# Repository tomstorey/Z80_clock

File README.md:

# Z80 based, triple time zone clock

This repository contains design files and source code for a clock project which uses a Z80 processor, and can display upto three different time zones at once.

All code is written in Z80 assembly, and can be assembled with the zasm assembler available at:

https://k1.spdns.de/Develop/Projects/zasm/Distributions/

Other assemblers may work, perhaps with minor modification to the code.

The display is made up of three rows of eight 16-segment displays, and is driven by a shift register of 136 bits (128 for display segments plus 8 for the dot points of the displays) so that an entire row is driven all at once.

Within the clock is a [Texas Instruments BQ4845 Real Time Clock](http://www.ti.com/product/BQ4845). A backup battery maintains the time while the power is off. The RTC time and date is configured to represent UTC, and each time zone is then calculated as an offset from UTC, either positive or negative.

Three ROMs provide all of the non-volatile storage needs:

 1. App ROM contains the application code
 2. TZ ROM contains time zone information
 3. Char ROM contains data for displaying characters

The following table describes the address ranges covered by each of the memories:

|              | Start  | End    | Size |
| ------------ | ------:| ------:| ----:|
| **App ROM**  | 0x0000 | 0x5FFF |  24K |
| **RAM**      | 0x6000 | 0x9FFF |  16K |
| **TZ ROM**   | 0xC000 | 0xDFFF |   8K |
| **Char ROM** | 0xE000 | 0xFFFF |   8K |

DIP switches allow each row of the display to be configured to any time or date according to entries stored within the TZ ROM.

## Source code structure/explanation
Assembly source files end with the `.s` extension. `.inc` files provide defines/equates and macros.

`clock.s` is the top source file, which includes a variety of `.inc` and other `.s` files to build up the entire application.

Other files in no particular order:

`configr_app.s` implements an "application" of sorts which allows the user to configure the time and date of the RTC.

`clock_app.s` also implements an "application" of sorts, the clock itself.

`c_lib.s` is an implementation of a couple of C-esque functions to copy blocks of memory and null terminated strings.

`ctc_isr.s` is where all of the Interrupt Service Routines for the CTC timer/counter channels live.

`platform.inc` provides information about the memory locations and sizes - this was particularly important during development as I was using a custom serial loader (`serial_mon.s`) to transfer and execute code from RAM, and needed to define different memory locations and sizes based on whether the code was assembled for serial loading or not.

`clock.inc` provides a lot of detail about the clock hardware, such as the addresses of various I/O peripherals. Included are also a variety of macros that provide basic mutex and sempahore functionality, among others.

Other `.inc` files define setting for control registers of various peripherals.

### Software architecture notes
The software implements some rudimentary "task" infrastructure intended to make it more modular and easily maintainable.

To achieve this, some macros are provided for scheduling and descheduling "tasks" and "applications". Although they are essentially the same thing, I have two basic rules to differentiate them:

 - Tasks are scheduled and descheduled to run only when required
 - Applications should be scheduled and never descheduled

For example, the configr and clock tasks are considered two applications because they are scheduled when the clock starts up, and never technically descheduled, however, only one of them will "run" at any one time, which brings me to the next topic...

Basic locking and signalling infrastructure is also provided through some semaphore and mutex macros.

Semaphores can be used to signal one piece of code from another piece of code. A specific example of the use of semaphores in this clock is between the clock application and the per-minute ISR from the RTC. The clock app signals to the ISR that it wants to know when the per-minute interrupt has occurred, and the ISR reciprocates by signalling to the application that it has occurred. This is achieved through two semaphores: 1. for the application to signal it wants to know when an interrupt has occurred, 2. for the ISR to signal the interrupt has occurred. Other uses of semaphores include signalling to various tasks when they should run.

Mutexes are used to lock resouces so that only one piece of code may use them at any one time. A particular use of mutexes in this clock is to determine which application "owns the foreground", or in other words, who can write to display buffers and read button states. The first application to acquire the foreground mutex can then hold onto it for as long as it wants (usually until the user presses the Esc button to switch between the clock and the configr apps).

### Utilities

There are a couple of small Python based utilities included as well, which were used during development, and in conjunction with `serial_mon.s`:

`loader.py` is used to load a `.rom` (i.e. binary) file into RAM and optionally execute it. This tool was used heavily and has had the most development. Each time I would build a new version of the clock software I would hit the reset button and use this tool to load the code into RAM and execute it.

`execer.py` is essentially the execute portion of the above, and simply tells the serial monitor to jump to a certain address. Could be used after a reset to simply re-execute the code without having to reload it.

`sender.py` is used to send bytes, and was used mostly during development of the serial monitor itself.

`reader.py` was intended to provide an ability to read back a portion of memory, but is in an unknown state at this time and the matching functionality is not implemented in the current serial loader.

## Hardware designs/schematics
Hardware designs are functional and complete. There are no PCB designs as the prototype hardware was built as rats nest on proto boards.

At time of writing, the following TODO list remains:

 - Determine best way to drive the speaker - there is a free CTC channel which could be used for this?

Otherwise, here are some lightweight descriptions of the schematic files:

`CPU board *.sch` contains the processor and all memories (RAM/ROMs), reset circuitry, oscillator, and power input.

`timer rtc io.sch` is a module which contains the RTC, a Z80 CTC peripheral, and user interface inputs such as buttons and DIP switches. It also has the speaker. The RTC also includes a watchdog reset function.

`display driver rev X.sch` contains all of the shift registers to drive all display segments on one row. Rev A implemented a discrete parallel-load to serial-output peripheral with 74HC595 shift registers for the drivers. Rev B changed the shift registers to TLC5916's (proper LED drivers) and also uses an ATF1502AS CPLD to implement the shift register logic. Both boards are functionally equivalent in that the CPU can simply OUT a byte and the shifter will automatically shift the byte out. Char ROM data may need to be inverted depending on which revision is in use - something I should probably make consistent, but notes are included in the char_rom.s file to help you figure that out in the mean time.

`uart board.sch` contains a Z80 SIO peripheral which was used for serial loading of code for execution from RAM. In a future revision I'll likely repurpose this to interface with a GPS module to perform time synchronisation to compensate for drift in the RTC.

There is currently no real schematic for the display board itself, this is a work in progress. I'll get around to it some day. :-)

## z80clock on MAME

A [MAME driver](https://github.com/mamedev/mame/blob/master/src/mame/drivers/z80clock.cpp)
to emulate for this project was added by
[Phill (@smf)](https://github.com/smf-) for his
[Using MAME as a development tool](https://www.meetup.com/london-retro-computing/events/282682483/)
presentation to the
[London Retro Computing Meetup](https://www.meetup.com/london-retro-computing/)

If you don't already have MAME get it from
[MAMEdev.org](https://www.mamedev.org/). The z80clock driver has been present
since MAME 0.239.

To run the driver:

```
mame z80clock -cart1 clock.rom -cart2 tz_rom.rom -cart3 char_rom.rom
```

Assuming the roms (in the `source` directory) are in the current directory
and `mame` is on the path.

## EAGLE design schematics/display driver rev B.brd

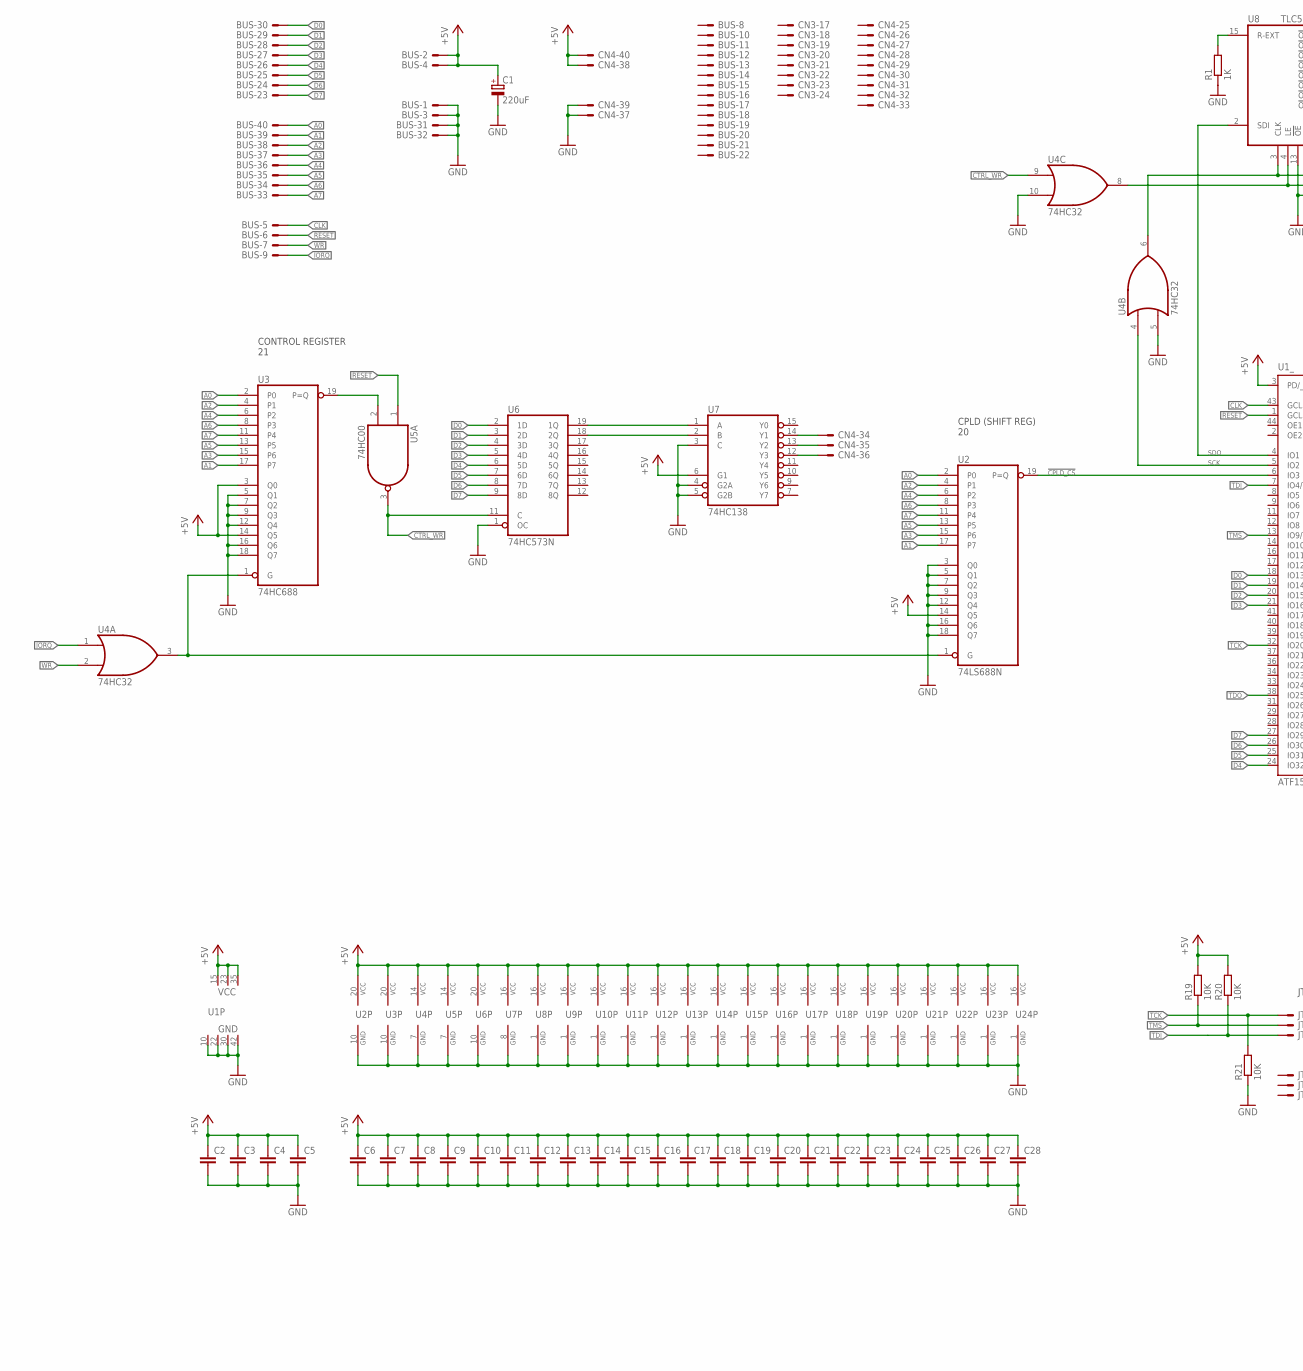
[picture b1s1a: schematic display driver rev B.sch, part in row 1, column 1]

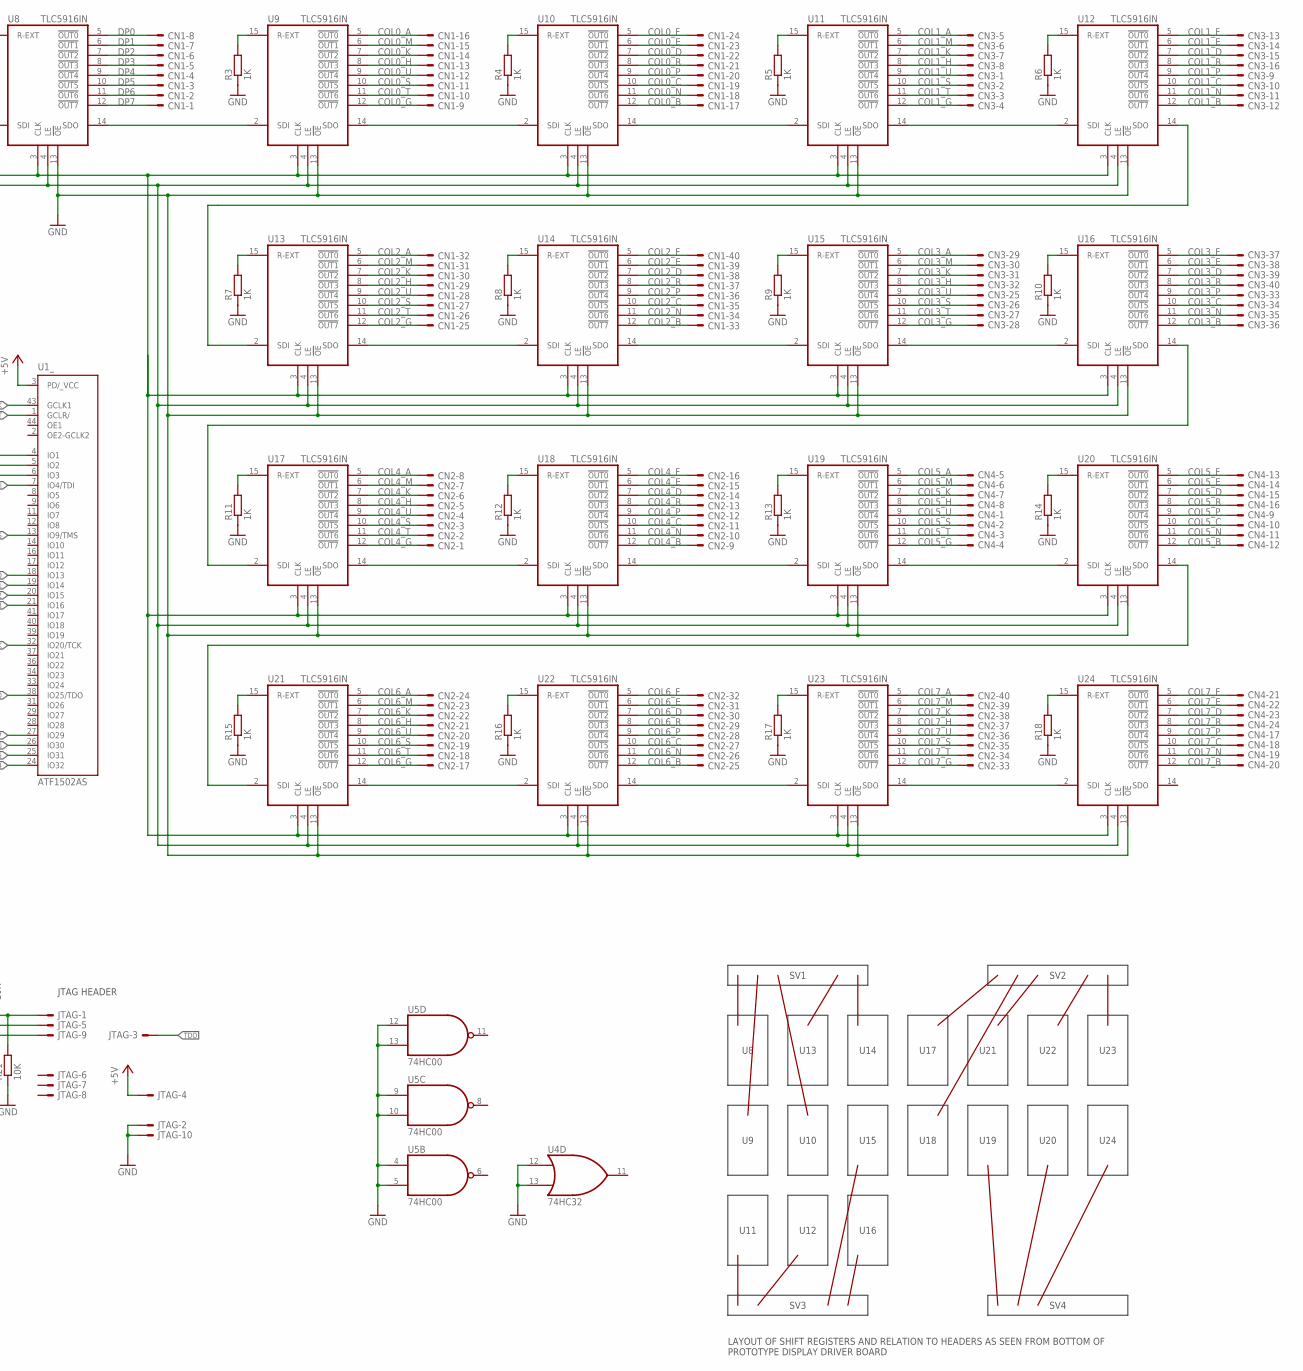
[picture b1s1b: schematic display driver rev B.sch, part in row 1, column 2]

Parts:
BUS: HDR40
C1: 220uF; E3,5-8
C2, C3, C4, C5, C6, C7, C8, C9, C10, C11, C12, C13, C14, C15, C16, C17, C18, C19, C20, C21, C22, C23, C24, C25, C26, C27, C28: C-EU050-025X075; C050-025X075
CN1, CN2, CN3, CN4: HDR40
JTAG: ML10E; ML10
R1, R3, R4, R5, R6, R7, R8, R9, R10, R11, R12, R13, R14, R15, R16, R17, R18: 1K; 0207/10
R19, R20, R21: 10K; 0207/10
U1: ATF1502AS; PLCC-S44
U2: 74LS688N; DIL20
U3: 74HC688; DIL20
U4: 74HC32; DIL14
U5: 74HC00; DIL14
U6: 74HC573N; DIL20
U7: 74HC138; DIL16
U8, U9, U10, U11, U12, U13, U14, U15, U16, U17, U18, U19, U20, U21, U22, U23, U24: TLC5916IN; DIL16

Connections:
!CPLD_CS!: U1.6 (IO3), U2.19 (P=Q)
!CTRL_WR!: U4.9 (I0), U5.3 (O), U6.11 (C)
!IORQ!: BUS.9, U4.1 (I0)
!RESET!: BUS.6, U1.1 (GCLR/), U5.1 (I0)
!WR!: BUS.7, U4.2 (I1)
+5V: BUS.2, BUS.4, C1.+, C2.1, C3.1, C4.1, C5.1, C6.1, C7.1, C8.1, C9.1, C10.1, C11.1, C12.1, C13.1, C14.1, C15.1, C16.1, C17.1, C18.1, C19.1, C20.1, C21.1, C22.1, C23.1, C24.1, C25.1, C26.1, C27.1, C28.1, CN4.38, CN4.40, JTAG.4, R19.2, R20.2, U1.3 (PD/_VCC), U1.15 (VCC), U1.23 (VCC), U1.35 (VCC), U2.14 (Q5), U2.20 (VCC), U3.3 (Q0), U3.14 (Q5), U3.20 (VCC), U4.14 (VCC), U5.14 (VCC), U6.20 (VCC), U7.6 (G1), U7.16 (VCC), U8.16 (VCC), U9.16 (VCC), U10.16 (VCC), U11.16 (VCC), U12.16 (VCC), U13.16 (VCC), U14.16 (VCC), U15.16 (VCC), U16.16 (VCC), U17.16 (VCC), U18.16 (VCC), U19.16 (VCC), U20.16 (VCC), U21.16 (VCC), U22.16 (VCC), U23.16 (VCC), U24.16 (VCC)
A0: BUS.40, U2.2 (P0), U3.2 (P0)
A1: BUS.39, U2.17 (P7), U3.17 (P7)
A2: BUS.38, U2.4 (P1), U3.4 (P1)
A3: BUS.37, U2.15 (P6), U3.15 (P6)
A4: BUS.36, U2.6 (P2), U3.6 (P2)
A5: BUS.35, U2.13 (P5), U3.13 (P5)
A6: BUS.34, U2.8 (P3), U3.8 (P3)
A7: BUS.33, U2.11 (P4), U3.11 (P4)
CLK: BUS.5, U1.43 (GCLK1)
COL0_A: CN1.16, U9.5 (!OUT0!)
COL0_B: CN1.17, U10.12 (!OUT7!)
COL0_C: CN1.19, U10.10 (!OUT5!)
COL0_D: CN1.22, U10.7 (!OUT2!)
COL0_E: CN1.23, U10.6 (!OUT1!)
COL0_F: CN1.24, U10.5 (!OUT0!)
COL0_G: CN1.9, U9.12 (!OUT7!)
COL0_H: CN1.13, U9.8 (!OUT3!)
COL0_K: CN1.14, U9.7 (!OUT2!)
COL0_M: CN1.15, U9.6 (!OUT1!)
COL0_N: CN1.18, U10.11 (!OUT6!)
COL0_P: CN1.20, U10.9 (!OUT4!)
COL0_R: CN1.21, U10.8 (!OUT3!)
COL0_S: CN1.11, U9.10 (!OUT5!)
COL0_T: CN1.10, U9.11 (!OUT6!)
COL0_U: CN1.12, U9.9 (!OUT4!)
COL1_A: CN3.5, U11.5 (!OUT0!)
COL1_B: CN3.12, U12.12 (!OUT7!)
COL1_C: CN3.10, U12.10 (!OUT5!)
COL1_D: CN3.15, U12.7 (!OUT2!)
COL1_E: CN3.14, U12.6 (!OUT1!)
COL1_F: CN3.13, U12.5 (!OUT0!)
COL1_G: CN3.4, U11.12 (!OUT7!)
COL1_H: CN3.8, U11.8 (!OUT3!)
COL1_K: CN3.7, U11.7 (!OUT2!)
COL1_M: CN3.6, U11.6 (!OUT1!)
COL1_N: CN3.11, U12.11 (!OUT6!)
COL1_P: CN3.9, U12.9 (!OUT4!)
COL1_R: CN3.16, U12.8 (!OUT3!)
COL1_S: CN3.2, U11.10 (!OUT5!)
COL1_T: CN3.3, U11.11 (!OUT6!)
COL1_U: CN3.1, U11.9 (!OUT4!)
COL2_A: CN1.32, U13.5 (!OUT0!)
COL2_B: CN1.33, U14.12 (!OUT7!)
COL2_C: CN1.35, U14.10 (!OUT5!)
COL2_D: CN1.38, U14.7 (!OUT2!)
COL2_E: CN1.39, U14.6 (!OUT1!)
COL2_F: CN1.40, U14.5 (!OUT0!)
COL2_G: CN1.25, U13.12 (!OUT7!)
COL2_H: CN1.29, U13.8 (!OUT3!)
COL2_K: CN1.30, U13.7 (!OUT2!)
COL2_M: CN1.31, U13.6 (!OUT1!)
COL2_N: CN1.34, U14.11 (!OUT6!)
COL2_P: CN1.36, U14.9 (!OUT4!)
COL2_R: CN1.37, U14.8 (!OUT3!)
COL2_S: CN1.27, U13.10 (!OUT5!)
COL2_T: CN1.26, U13.11 (!OUT6!)
COL2_U: CN1.28, U13.9 (!OUT4!)
COL3_A: CN3.29, U15.5 (!OUT0!)
COL3_B: CN3.36, U16.12 (!OUT7!)
COL3_C: CN3.34, U16.10 (!OUT5!)
COL3_D: CN3.39, U16.7 (!OUT2!)
COL3_E: CN3.38, U16.6 (!OUT1!)
COL3_F: CN3.37, U16.5 (!OUT0!)
COL3_G: CN3.28, U15.12 (!OUT7!)
COL3_H: CN3.32, U15.8 (!OUT3!)
COL3_K: CN3.31, U15.7 (!OUT2!)
COL3_M: CN3.30, U15.6 (!OUT1!)
COL3_N: CN3.35, U16.11 (!OUT6!)
COL3_P: CN3.33, U16.9 (!OUT4!)
COL3_R: CN3.40, U16.8 (!OUT3!)
COL3_S: CN3.26, U15.10 (!OUT5!)
COL3_T: CN3.27, U15.11 (!OUT6!)
COL3_U: CN3.25, U15.9 (!OUT4!)
COL4_A: CN2.8, U17.5 (!OUT0!)
COL4_B: CN2.9, U18.12 (!OUT7!)
COL4_C: CN2.11, U18.10 (!OUT5!)
COL4_D: CN2.14, U18.7 (!OUT2!)
COL4_E: CN2.15, U18.6 (!OUT1!)
COL4_F: CN2.16, U18.5 (!OUT0!)
COL4_G: CN2.1, U17.12 (!OUT7!)
COL4_H: CN2.5, U17.8 (!OUT3!)
COL4_K: CN2.6, U17.7 (!OUT2!)
COL4_M: CN2.7, U17.6 (!OUT1!)
COL4_N: CN2.10, U18.11 (!OUT6!)
COL4_P: CN2.12, U18.9 (!OUT4!)
COL4_R: CN2.13, U18.8 (!OUT3!)
COL4_S: CN2.3, U17.10 (!OUT5!)
COL4_T: CN2.2, U17.11 (!OUT6!)
COL4_U: CN2.4, U17.9 (!OUT4!)
COL5_A: CN4.5, U19.5 (!OUT0!)
COL5_B: CN4.12, U20.12 (!OUT7!)
COL5_C: CN4.10, U20.10 (!OUT5!)
COL5_D: CN4.15, U20.7 (!OUT2!)
COL5_E: CN4.14, U20.6 (!OUT1!)
COL5_F: CN4.13, U20.5 (!OUT0!)
COL5_G: CN4.4, U19.12 (!OUT7!)
COL5_H: CN4.8, U19.8 (!OUT3!)
COL5_K: CN4.7, U19.7 (!OUT2!)
COL5_M: CN4.6, U19.6 (!OUT1!)
COL5_N: CN4.11, U20.11 (!OUT6!)
COL5_P: CN4.9, U20.9 (!OUT4!)
COL5_R: CN4.16, U20.8 (!OUT3!)
COL5_S: CN4.2, U19.10 (!OUT5!)
COL5_T: CN4.3, U19.11 (!OUT6!)
COL5_U: CN4.1, U19.9 (!OUT4!)
COL6_A: CN2.24, U21.5 (!OUT0!)
COL6_B: CN2.25, U22.12 (!OUT7!)
COL6_C: CN2.27, U22.10 (!OUT5!)
COL6_D: CN2.30, U22.7 (!OUT2!)
COL6_E: CN2.31, U22.6 (!OUT1!)
COL6_F: CN2.32, U22.5 (!OUT0!)
COL6_G: CN2.17, U21.12 (!OUT7!)
COL6_H: CN2.21, U21.8 (!OUT3!)
COL6_K: CN2.22, U21.7 (!OUT2!)
COL6_M: CN2.23, U21.6 (!OUT1!)
COL6_N: CN2.26, U22.11 (!OUT6!)
COL6_P: CN2.28, U22.9 (!OUT4!)
COL6_R: CN2.29, U22.8 (!OUT3!)
COL6_S: CN2.19, U21.10 (!OUT5!)
COL6_T: CN2.18, U21.11 (!OUT6!)
COL6_U: CN2.20, U21.9 (!OUT4!)
COL7_A: CN2.40, U23.5 (!OUT0!)
COL7_B: CN4.20, U24.12 (!OUT7!)
COL7_C: CN4.18, U24.10 (!OUT5!)
COL7_D: CN4.23, U24.7 (!OUT2!)
COL7_E: CN4.22, U24.6 (!OUT1!)
COL7_F: CN4.21, U24.5 (!OUT0!)
COL7_G: CN2.33, U23.12 (!OUT7!)
COL7_H: CN2.37, U23.8 (!OUT3!)
COL7_K: CN2.38, U23.7 (!OUT2!)
COL7_M: CN2.39, U23.6 (!OUT1!)
COL7_N: CN4.19, U24.11 (!OUT6!)
COL7_P: CN4.17, U24.9 (!OUT4!)
COL7_R: CN4.24, U24.8 (!OUT3!)
COL7_S: CN2.35, U23.10 (!OUT5!)
COL7_T: CN2.34, U23.11 (!OUT6!)
COL7_U: CN2.36, U23.9 (!OUT4!)
D0: BUS.30, U1.18 (IO13), U6.2 (1D)
D1: BUS.29, U1.19 (IO14), U6.3 (2D)
D2: BUS.28, U1.20 (IO15), U6.4 (3D)
D3: BUS.27, U1.21 (IO16), U6.5 (4D)
D4: BUS.26, U1.24 (IO32), U6.6 (5D)
D5: BUS.25, U1.25 (IO31), U6.7 (6D)
D6: BUS.24, U1.26 (IO30), U6.8 (7D)
D7: BUS.23, U1.27 (IO29), U6.9 (8D)
DP0: CN1.8, U8.5 (!OUT0!)
DP1: CN1.7, U8.6 (!OUT1!)
DP2: CN1.6, U8.7 (!OUT2!)
DP3: CN1.5, U8.8 (!OUT3!)
DP4: CN1.4, U8.9 (!OUT4!)
DP5: CN1.3, U8.10 (!OUT5!)
DP6: CN1.2, U8.11 (!OUT6!)
DP7: CN1.1, U8.12 (!OUT7!)
GND: BUS.1, BUS.3, BUS.31, BUS.32, C1.-, C2.2, C3.2, C4.2, C5.2, C6.2, C7.2, C8.2, C9.2, C10.2, C11.2, C12.2, C13.2, C14.2, C15.2, C16.2, C17.2, C18.2, C19.2, C20.2, C21.2, C22.2, C23.2, C24.2, C25.2, C26.2, C27.2, C28.2, CN4.37, CN4.39, JTAG.2, JTAG.10, R1.1, R3.1, R4.1, R5.1, R6.1, R7.1, R8.1, R9.1, R10.1, R11.1, R12.1, R13.1, R14.1, R15.1, R16.1, R17.1, R18.1, R21.1, U1.10 (GND), U1.22 (GND), U1.30 (GND), U1.42 (GND), U2.3 (Q0), U2.5 (Q1), U2.7 (Q2), U2.9 (Q3), U2.10 (GND), U2.12 (Q4), U2.16 (Q6), U2.18 (Q7), U3.5 (Q1), U3.7 (Q2), U3.9 (Q3), U3.10 (GND), U3.12 (Q4), U3.16 (Q6), U3.18 (Q7), U4.5 (I1), U4.7 (GND), U4.10 (I1), U4.12 (I0), U4.13 (I1), U5.4 (I0), U5.5 (I1), U5.7 (GND), U5.9 (I0), U5.10 (I1), U5.12 (I0), U5.13 (I1), U6.1 (OC), U6.10 (GND), U7.3 (C), U7.4 (G2A), U7.5 (G2B), U7.8 (GND), U8.1 (GND), U8.13 (!OE!), U9.1 (GND), U9.13 (!OE!), U10.1 (GND), U10.13 (!OE!), U11.1 (GND), U11.13 (!OE!), U12.1 (GND), U12.13 (!OE!), U13.1 (GND), U13.13 (!OE!), U14.1 (GND), U14.13 (!OE!), U15.1 (GND), U15.13 (!OE!), U16.1 (GND), U16.13 (!OE!), U17.1 (GND), U17.13 (!OE!), U18.1 (GND), U18.13 (!OE!), U19.1 (GND), U19.13 (!OE!), U20.1 (GND), U20.13 (!OE!), U21.1 (GND), U21.13 (!OE!), U22.1 (GND), U22.13 (!OE!), U23.1 (GND), U23.13 (!OE!), U24.1 (GND), U24.13 (!OE!)
unnamed: U3.19 (P=Q), U4.6 (O), U5.2 (I1), U8.3 (CLK), U9.3 (CLK), U10.3 (CLK), U11.3 (CLK), U12.3 (CLK), U13.3 (CLK), U14.3 (CLK), U15.3 (CLK), U16.3 (CLK), U17.3 (CLK), U18.3 (CLK), U19.3 (CLK), U20.3 (CLK), U21.3 (CLK), U22.3 (CLK), U23.3 (CLK), U24.3 (CLK)
unnamed: CN4.34, U7.14 (Y1)
unnamed: U6.19 (1Q), U7.1 (A)
unnamed: U6.18 (2Q), U7.2 (B)
unnamed: CN4.35, U7.13 (Y2)
unnamed: CN4.36, U7.12 (Y3)
unnamed: R1.2, U8.15 (R-EXT)
unnamed: R3.2, U9.15 (R-EXT)
unnamed: R4.2, U10.15 (R-EXT)
unnamed: R5.2, U11.15 (R-EXT)
unnamed: R6.2, U12.15 (R-EXT)
unnamed: R7.2, U13.15 (R-EXT)
unnamed: R8.2, U14.15 (R-EXT)
unnamed: R9.2, U15.15 (R-EXT)
unnamed: R10.2, U16.15 (R-EXT)
unnamed: R11.2, U17.15 (R-EXT)
unnamed: R12.2, U18.15 (R-EXT)
unnamed: R13.2, U19.15 (R-EXT)
unnamed: R14.2, U20.15 (R-EXT)
unnamed: R15.2, U21.15 (R-EXT)
unnamed: R16.2, U22.15 (R-EXT)
unnamed: R17.2, U23.15 (R-EXT)
unnamed: R18.2, U24.15 (R-EXT)
unnamed: U8.14 (SDO), U9.2 (SDI)
unnamed: U9.14 (SDO), U10.2 (SDI)
unnamed: U10.14 (SDO), U11.2 (SDI)
unnamed: U11.14 (SDO), U12.2 (SDI)
unnamed: U13.14 (SDO), U14.2 (SDI)
unnamed: U14.14 (SDO), U15.2 (SDI)
unnamed: U15.14 (SDO), U16.2 (SDI)
unnamed: U17.14 (SDO), U18.2 (SDI)
unnamed: U18.14 (SDO), U19.2 (SDI)
unnamed: U19.14 (SDO), U20.2 (SDI)
unnamed: U21.14 (SDO), U22.2 (SDI)
unnamed: U22.14 (SDO), U23.2 (SDI)
unnamed: U23.14 (SDO), U24.2 (SDI)
unnamed: U4.8 (O), U8.4 (LE), U9.4 (LE), U10.4 (LE), U11.4 (LE), U12.4 (LE), U13.4 (LE), U14.4 (LE), U15.4 (LE), U16.4 (LE), U17.4 (LE), U18.4 (LE), U19.4 (LE), U20.4 (LE), U21.4 (LE), U22.4 (LE), U23.4 (LE), U24.4 (LE)
unnamed: U12.14 (SDO), U13.2 (SDI)
unnamed: U16.14 (SDO), U17.2 (SDI)
unnamed: U20.14 (SDO), U21.2 (SDI)
unnamed: U2.1 (G), U3.1 (G), U4.3 (O)
SCK: U1.5 (IO2), U4.4 (I0)
SDO: U1.4 (IO1), U8.2 (SDI)
TCK: JTAG.1, R21.2, U1.32 (IO20/TCK)
TDI: JTAG.9, R20.1, U1.7 (IO4/TDI)
TDO: JTAG.3, U1.38 (IO25/TDO)
TMS: JTAG.5, R19.1, U1.13 (IO9/TMS)

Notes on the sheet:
SV1
SV2
SV3
SV4
U13
U14
U17
U21
U22
U23
U24
U20
U19
U18
U15
U10
U11
U12
U16
LAYOUT OF SHIFT REGISTERS AND RELATION TO HEADERS AS SEEN FROM BOTTOM OF PROTOTYPE DISPLAY DRIVER BOARD
CONTROL REGISTER 21
CPLD (SHIFT REG) 20
JTAG HEADER

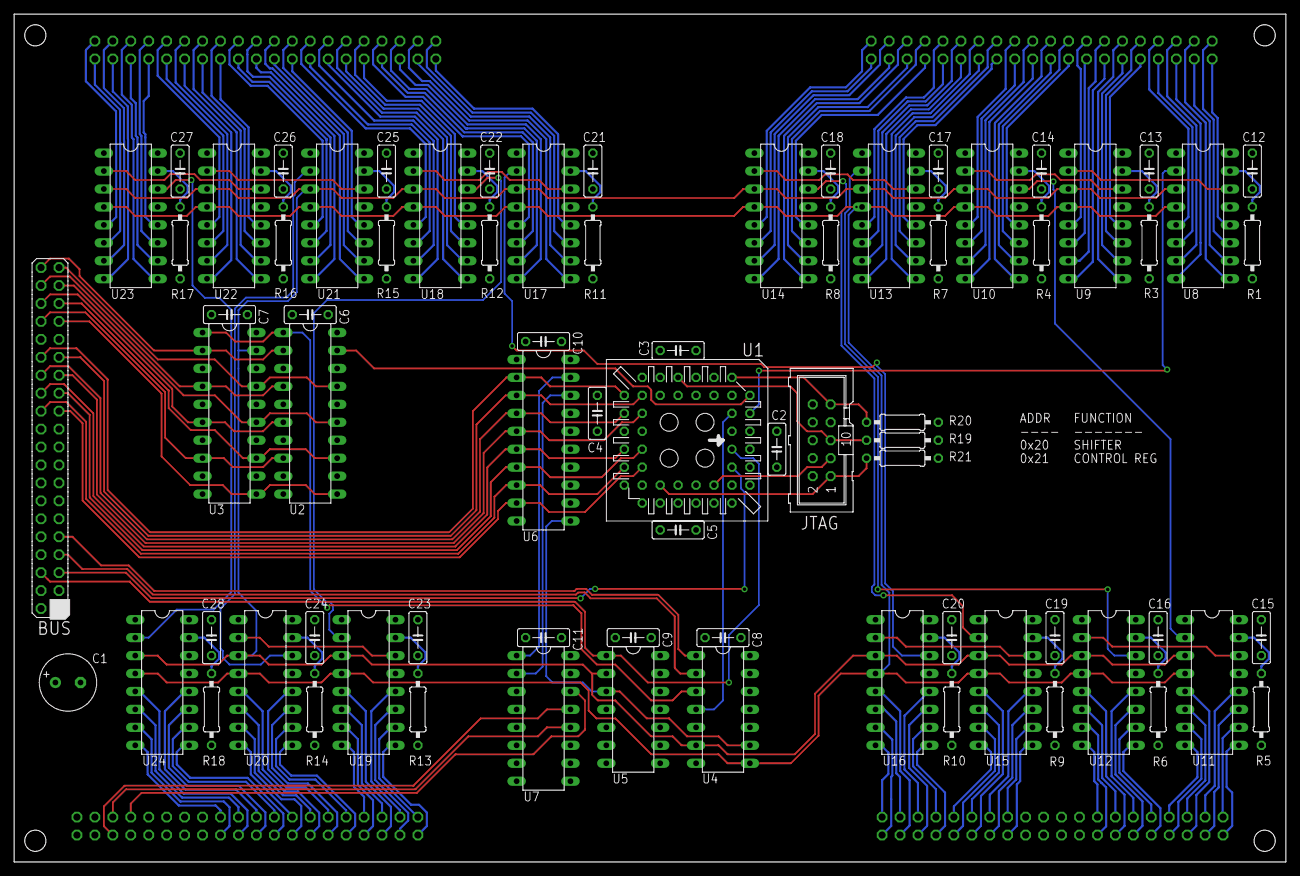
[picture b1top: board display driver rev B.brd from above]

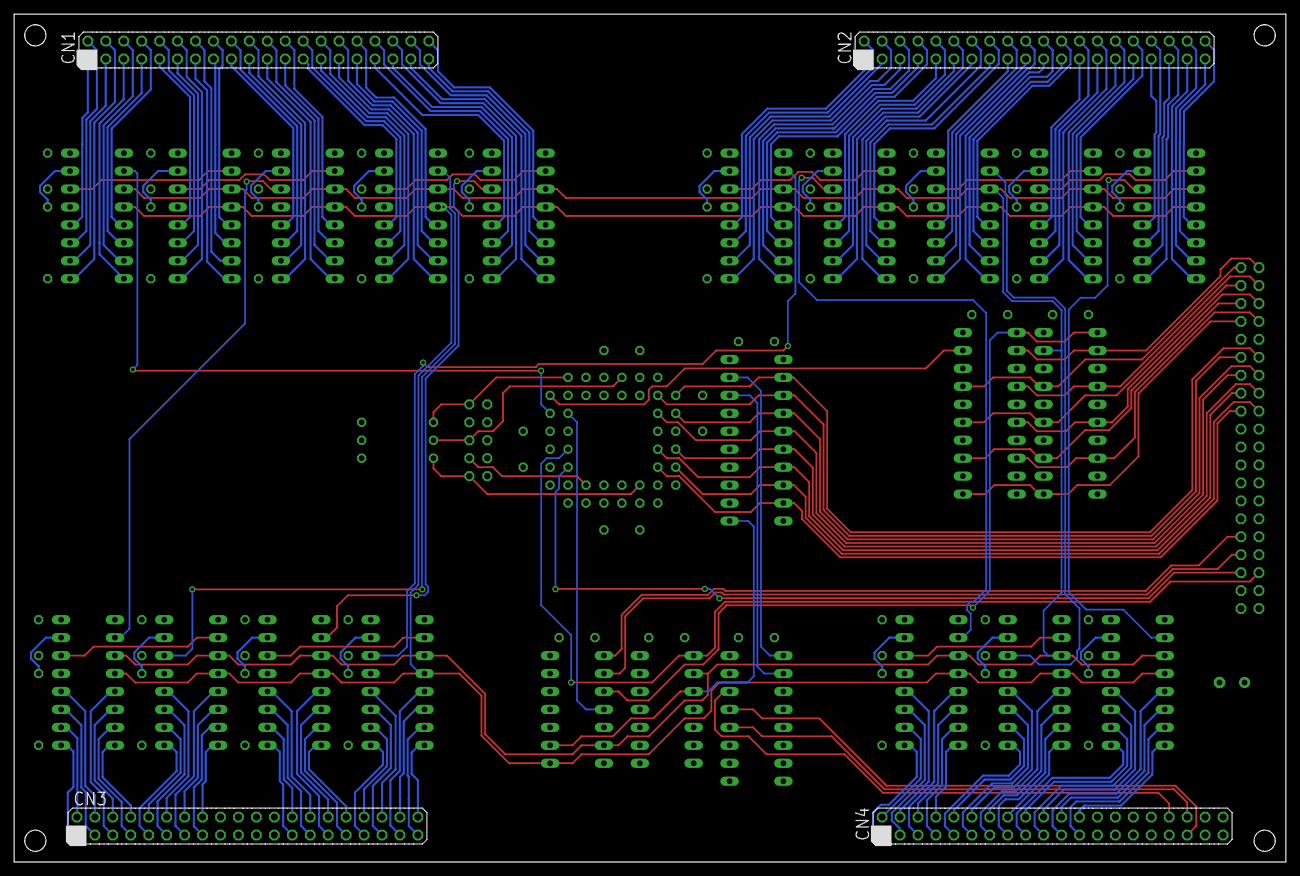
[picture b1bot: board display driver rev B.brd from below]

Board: 4 copper layers, 180.0 x 120.0 mm, 78 parts (4 on the bottom side), 207 nets.

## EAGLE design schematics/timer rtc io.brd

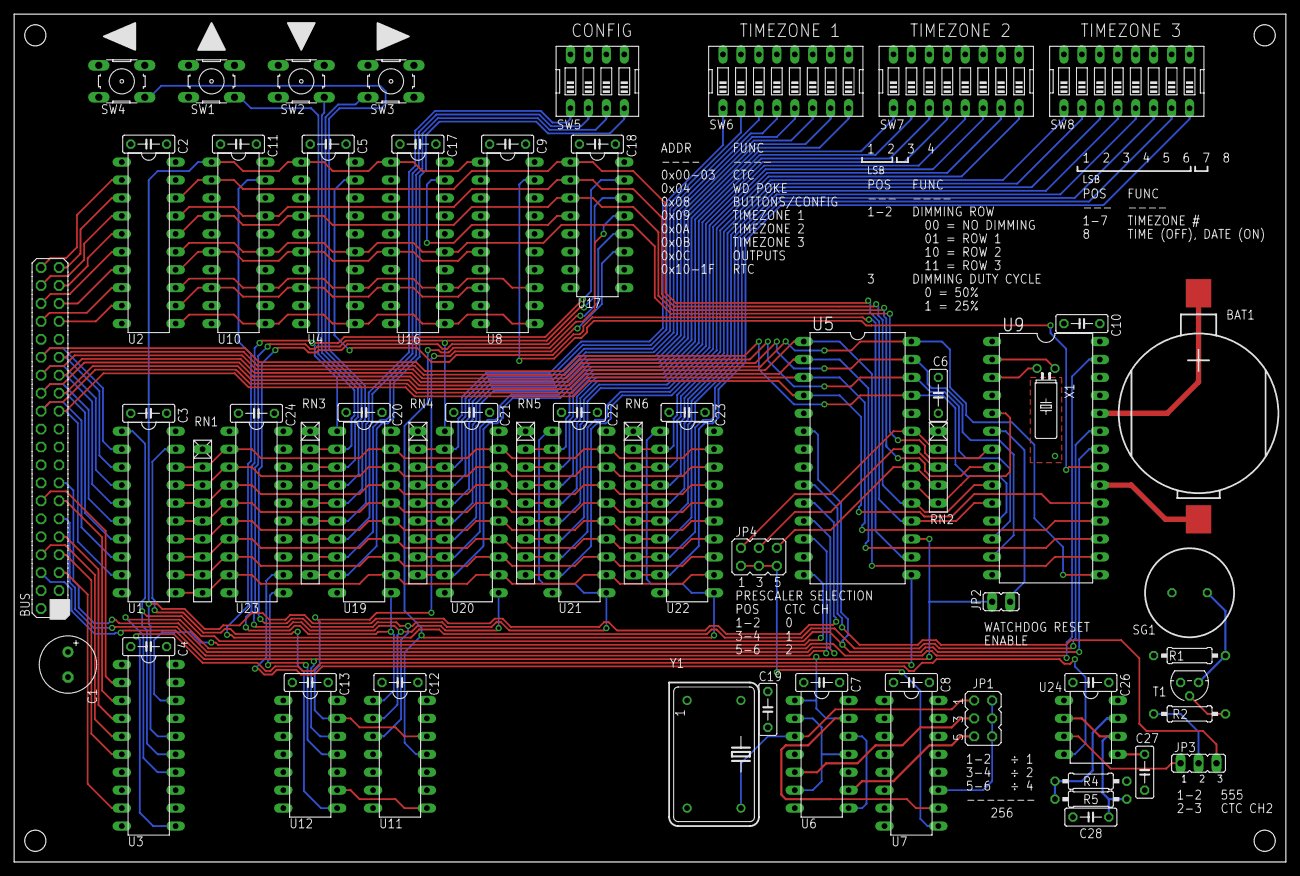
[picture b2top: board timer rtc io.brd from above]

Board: 4 copper layers, 180.0 x 120.0 mm, 72 parts (0 on the bottom side), 116 nets.

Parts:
BAT1: CR2032; CR2032-SMD
BUS: HDR40
C1: 220uF; E3,5-8
C2, C3, C4, C5, C6, C7, C8, C9, C10, C11, C12, C13, C17, C18, C19, C20, C21, C22, C23, C24, C26, C27, C28: 100nF; C050-025X075
JP1, JP4: JP3Q
JP2: JP1
JP3: JP2
R1, R2: 1K; 0207/10
R4, R5: 560R; 0207/10
RN1, RN3, RN4, RN5, RN6: 10K; RN-9
RN2: 10K; RN-5
SG1: PKM13EPYH4000X; PKM13EPYH400X
SW1, SW2, SW3, SW4: B3F-10XX
SW5: EDG-04
SW6, SW7, SW8: EDG-08
T1: BC547; TO92
U1, U2, U3: 74HC245; DIL20
U4, U8, U10, U16: 74HC688; DIL20
U5: Z84C30; DIL28
U6: 74HC74; DIL14
U7: 74HC590; DIL16
U9: BQ4845; DIL28-6
U11: 74HC30; DIL14
U12: 74HC00; DIL14
U17: 74HC138; DIL16
U19, U20, U21, U22, U23: 74HC573; DIL20
U24: NE555; DIL-08
X1: 32.768KHz; TC38H
Y1: 4.096MHz; DIL14S

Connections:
!IEO!: BUS.15, U5.11
!INT!: BUS.11, U5.12
!IORQ!: U3.16, U4.1, U5.10, U8.1, U10.1, U16.1
!M1!: U3.18, U5.14
!OBD!: U1.19, U12.8
!RD!: U1.1, U3.15, U5.6, U9.22
!RESET!: BUS.6, JP2.1, U5.17, U6.1, U6.13, U7.10, U12.12
!WR!: U3.14, U9.27
+5V: BUS.2, BUS.4, C1.+, C2.1, C3.1, C4.1, C5.1, C6.1, C7.1, C8.1, C9.1, C10.1, C11.1, C12.1, C13.1, C17.1, C18.1, C19.1, C20.1, C21.1, C22.1, C23.1, C24.1, C26.1, R1.2, R4.2, RN2.1, RN3.1, RN4.1, RN5.1, RN6.1, SG1.1, U1.20, U2.1, U2.20, U3.1, U3.20, U4.20, U5.13, U5.24, U6.4, U6.10, U6.14, U7.16, U8.7, U8.20, U9.26, U9.28, U10.5, U10.20, U11.4, U11.5, U11.6, U11.14, U12.10, U12.14, U16.16, U16.20, U17.6, U17.16, U19.20, U20.20, U21.20, U22.20, U23.20, U24.8, Y1.14
A0: U2.18, U5.18, U9.10, U10.2, U17.1
A1: U2.17, U5.19, U9.9, U10.17, U17.2
A2: U2.16, U4.4, U9.8, U10.4, U17.3
A3: U2.15, U4.15, U9.7, U10.15, U16.15
A4: U2.14, U4.6, U8.6, U10.6, U16.6
A5: U2.13, U4.13, U8.13, U10.13, U16.13
A6: U2.12, U4.8, U8.8, U10.8, U16.8
A7: U2.11, U4.11, U8.11, U10.11, U16.11
CLK: U3.11, U5.15
CTC_CH2: JP3.3, U5.9
D0: RN1.2, U1.18, U19.19, U20.19, U21.19, U22.19, U23.2
D0`: BUS.30, U1.2, U5.25, U9.11
D1: RN1.3, U1.17, U19.18, U20.18, U21.18, U22.18, U23.3
D1`: BUS.29, U1.3, U5.26, U9.12
D2: RN1.4, U1.16, U19.17, U20.17, U21.17, U22.17, U23.4
D2`: BUS.28, U1.4, U5.27, U9.13
D3: RN1.5, U1.15, U19.16, U20.16, U21.16, U22.16, U23.5
D3`: BUS.27, U1.5, U5.28, U9.15
D4: RN1.6, U1.14, U19.15, U20.15, U21.15, U22.15, U23.6
D4`: BUS.26, U1.6, U5.1, U9.16
D5: RN1.7, U1.13, U19.14, U20.14, U21.14, U22.14, U23.7
D5`: BUS.25, U1.7, U5.2, U9.17
D6: RN1.8, U1.12, U19.13, U20.13, U21.13, U22.13, U23.8
D6`: BUS.24, U1.8, U5.3, U9.18
D7: RN1.9, U1.11, U19.12, U20.12, U21.12, U22.12, U23.9
D7`: BUS.23, U1.9, U5.4, U9.19
GND: BAT1.-, BUS.1, BUS.3, C1.-, C2.2, C3.2, C4.2, C5.2, C6.2, C7.2, C8.2, C9.2, C10.2, C11.2, C12.2, C13.2, C17.2, C18.2, C19.2, C20.2, C21.2, C22.2, C23.2, C24.2, C26.2, C27.2, C28.2, RN1.1, SW1.1, SW1.2, SW2.1, SW2.2, SW3.1, SW3.2, SW4.1, SW4.2, SW5.5, SW5.6, SW5.7, SW5.8, SW6.9, SW6.10, SW6.11, SW6.12, SW6.13, SW6.14, SW6.15, SW6.16, SW7.9, SW7.10, SW7.11, SW7.12, SW7.13, SW7.14, SW7.15, SW7.16, SW8.9, SW8.10, SW8.11, SW8.12, SW8.13, SW8.14, SW8.15, SW8.16, T1.1, U1.10, U2.10, U2.19, U3.7, U3.8, U3.10, U3.19, U4.2, U4.3, U4.5, U4.7, U4.9, U4.10, U4.12, U4.14, U4.16, U4.17, U4.18, U5.5, U6.7, U7.8, U7.12, U7.13, U7.14, U8.2, U8.3, U8.4, U8.5, U8.9, U8.10, U8.12, U8.14, U8.15, U8.16, U8.17, U8.18, U9.14, U9.20, U10.3, U10.7, U10.9, U10.10, U10.12, U10.14, U10.16, U10.18, U11.7, U12.1, U12.2, U12.4, U12.5, U12.7, U16.2, U16.3, U16.4, U16.5, U16.7, U16.9, U16.10, U16.12, U16.14, U16.17, U16.18, U17.5, U17.8, U19.10, U20.10, U21.10, U22.10, U23.1, U23.10, U24.1, Y1.7
unnamed: U6.2, U6.6, U6.11
unnamed: U9.2, X1.1
unnamed: U9.23, U10.19
unnamed: U9.3, X1.2
unnamed: U11.8, U12.9
unnamed: BAT1.+, U9.24
unnamed: U8.19, U9.21
unnamed: U12.11, U23.11
unnamed: JP1.3, U6.5
unnamed: U16.19, U17.4
unnamed: JP4.4, RN2.3, U5.22
unnamed: RN4.2, SW6.1, U20.2
unnamed: RN4.3, SW6.2, U20.3
unnamed: RN4.4, SW6.3, U20.4
unnamed: RN4.5, SW6.4, U20.5
unnamed: RN4.6, SW6.5, U20.6
unnamed: RN4.7, SW6.6, U20.7
unnamed: RN4.8, SW6.7, U20.8
unnamed: RN4.9, SW6.8, U20.9
unnamed: RN5.2, SW7.1, U21.2
unnamed: RN5.3, SW7.2, U21.3
unnamed: RN5.4, SW7.3, U21.4
unnamed: RN5.5, SW7.4, U21.5
unnamed: RN5.6, SW7.5, U21.6
unnamed: RN5.7, SW7.6, U21.7
unnamed: RN5.8, SW7.7, U21.8
unnamed: RN5.9, SW7.8, U21.9
unnamed: RN6.2, SW8.1, U22.2
unnamed: RN6.3, SW8.2, U22.3
unnamed: RN6.4, SW8.3, U22.4
unnamed: RN6.5, SW8.4, U22.5
unnamed: RN6.6, SW8.5, U22.6
unnamed: RN6.7, SW8.6, U22.7
unnamed: RN6.8, SW8.7, U22.8
unnamed: RN6.9, SW8.8, U22.9
unnamed: JP1.5, U6.9
unnamed: RN3.2, SW1.4, U19.2
unnamed: RN3.3, SW2.4, U19.3
unnamed: RN3.4, SW3.3, U19.4
unnamed: RN3.5, SW4.4, U19.5
unnamed: RN3.6, SW5.1, U19.6
unnamed: RN3.7, SW5.2, U19.7
unnamed: RN3.8, SW5.3, U19.8
unnamed: RN3.9, SW5.4, U19.9
unnamed: U11.1, U17.15, U19.1, U19.11
unnamed: U11.2, U17.14, U20.1, U20.11
unnamed: U11.11, U17.13, U22.1, U22.11
unnamed: JP4.2, RN2.2, U5.23
unnamed: RN2.5, U5.20, U9.5
unnamed: JP2.2, U9.6
unnamed: U11.12, U12.13, U17.11
unnamed: C27.1, U24.5
unnamed: U23.12, U24.4
unnamed: JP1.1, U6.3, Y1.8
unnamed: U6.8, U6.12
unnamed: JP4.1, JP4.3, JP4.5, U7.9
unnamed: R1.1, SG1.2, T1.3
unnamed: JP3.1, U24.3
unnamed: JP3.2, R2.1
unnamed: JP1.2, JP1.4, JP1.6, U7.11
unnamed: U4.19, U5.16
unnamed: BUS.33, U2.9
unnamed: BUS.34, U2.8
unnamed: BUS.35, U2.7
unnamed: BUS.36, U2.6
unnamed: BUS.37, U2.5
unnamed: BUS.38, U2.4
unnamed: BUS.39, U2.3
unnamed: BUS.40, U2.2
unnamed: BUS.14, U3.2
unnamed: BUS.13, U3.3
unnamed: BUS.9, U3.4
unnamed: BUS.8, U3.5
unnamed: BUS.7, U3.6
unnamed: BUS.5, U3.9
unnamed: R2.2, T1.2
unnamed: R4.1, R5.2, U24.7
unnamed: C28.1, R5.1, U24.2, U24.6
unnamed: U11.3, U17.12, U21.1, U21.11
unnamed: JP4.6, RN2.4, U5.21
